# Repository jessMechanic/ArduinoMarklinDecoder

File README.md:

# espMarklinController

## goal

A cheap opensource decoder for the marklin model trains. based on atmelmega micro controller.

## status 

this is currently in a working condintion but open to implovements
this due to my own circumstances has only be tested on a 60651 Marklin Digital Mobil Station Controller.

## current state
- custom addres
- support for lights, sound and general functions keys.

## future plans
a smaller design of the pcb to give support for a wider support
change pcb design to support other than 5v motors (this can currently be fixed by using a jumper wire from the v-in to a lifted leg of the motor driver)

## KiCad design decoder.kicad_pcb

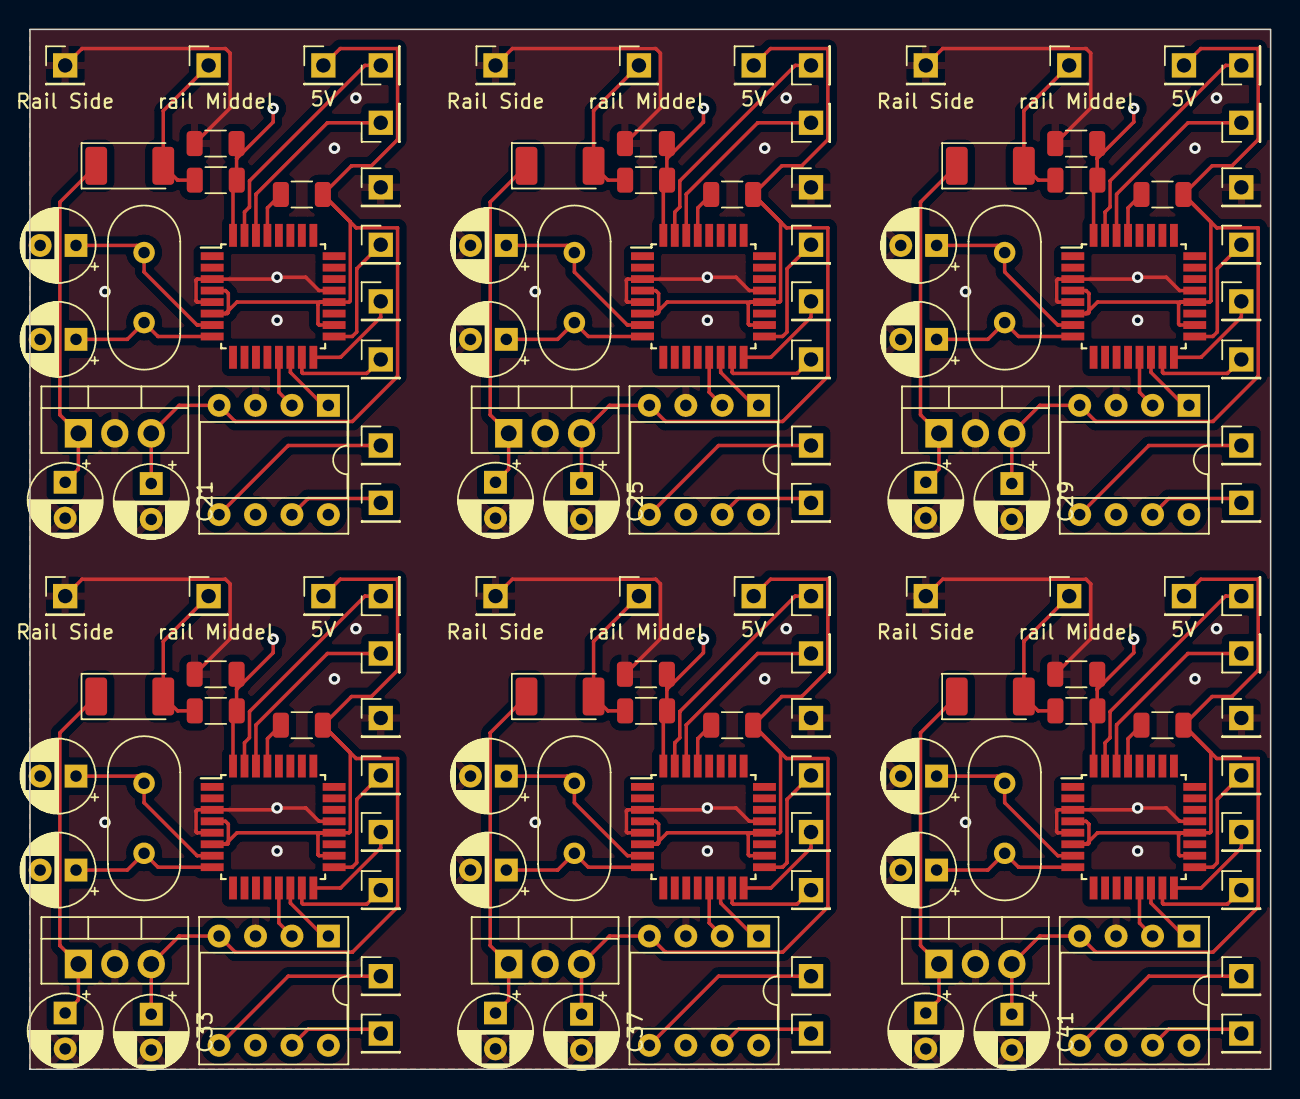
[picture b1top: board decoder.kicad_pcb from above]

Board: 2 copper layers, 86.5 x 72.5 mm, 138 parts (0 on the bottom side), 17 nets.

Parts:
C21, C25, C29, C33, C37, C41: 47uF; CP_Radial_D5.0mm_P2.50mm
C22, C26, C30, C34, C38, C42: 10uF; CP_Radial_D5.0mm_P2.50mm
C23, C24, C27, C28, C31, C32, C35, C36, C39, C40, C43, C44: 22pF; CP_Radial_D5.0mm_P2.50mm
D6, D7, D8, D9, D10, D11: D; D_2010_5025Metric_Pad1.52x2.65mm_HandSolder
R16, R19, R22, R25, R28, R31: 2.2k ohm; R_1206_3216Metric
R17, R18, R20, R21, R23, R24, R26, R27, R29, R30, R32, R33: 1k ohm; R_1206_3216Metric
S56, S67, S78, S89, S100, S111: LED +; PinHeader_1x01_P2.54mm_Vertical
S57, S68, S79, S90, S101, S112: GND; PinHeader_1x01_P2.54mm_Vertical
S58, S69, S80, S91, S102, S113: MotorB; PinHeader_1x01_P2.54mm_Vertical
S59, S70, S81, S92, S103, S114: MotorA; PinHeader_1x01_P2.54mm_Vertical
S60, S71, S82, S93, S104, S115: TX; PinHeader_1x01_P2.54mm_Vertical
S61, S72, S83, S94, S105, S116: RX; PinHeader_1x01_P2.54mm_Vertical
S62, S73, S84, S95, S106, S117: rail Middel; PinHeader_1x01_P2.54mm_Vertical
S63, S74, S85, S96, S107, S118: Rail Side; PinHeader_1x01_P2.54mm_Vertical
S64, S75, S86, S97, S108, S119: MOSI; PinHeader_1x01_P2.54mm_Vertical
S65, S76, S87, S98, S109, S120: MISO; PinHeader_1x01_P2.54mm_Vertical
S66, S77, S88, S99, S110, S121: 5V; PinHeader_1x01_P2.54mm_Vertical
U16, U19, U22, U25, U28, U31: ATmega8-16A; TQFP-32_7x7mm_P0.8mm
U17, U20, U23, U26, U29, U32: LF15_TO220; TO-220-3_Vertical
U18, U21, U24, U27, U30, U33: RZ7886; DIP-8_W7.62mm_Socket
Y6, Y7, Y8, Y9, Y10, Y11: Crystal 16k; Crystal_HC49-4H_Vertical

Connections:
+5V: C21.1, C25.1, C29.1, C33.1, C37.1, C41.1, R18.1, R21.1, R24.1, R27.1, R30.1, R33.1, S66.1 (K), S77.1 (K), S88.1 (K), S99.1 (K), S110.1 (K), S121.1 (K), U16.4 (VCC), U16.6 (VCC), U16.18 (AVCC), U16.20 (AREF), U17.3 (VO), U18.4 (Vcc), U19.4 (VCC), U19.6 (VCC), U19.18 (AVCC), U19.20 (AREF), U20.3 (VO), U21.4 (Vcc), U22.4 (VCC), U22.6 (VCC), U22.18 (AVCC), U22.20 (AREF), U23.3 (VO), U24.4 (Vcc), U25.4 (VCC), U25.6 (VCC), U25.18 (AVCC), U25.20 (AREF), U26.3 (VO), U27.4 (Vcc), U28.4 (VCC), U28.6 (VCC), U28.18 (AVCC), U28.20 (AREF), U29.3 (VO), U30.4 (Vcc), U31.4 (VCC), U31.6 (VCC), U31.18 (AVCC), U31.20 (AREF), U32.3 (VO), U33.4 (Vcc)
BI: U16.14 (PB2), U18.1 (BI), U19.14 (PB2), U21.1 (BI), U22.14 (PB2), U24.1 (BI), U25.14 (PB2), U27.1 (BI), U28.14 (PB2), U30.1 (BI), U31.14 (PB2), U33.1 (BI)
FI: U16.13 (PB1), U18.2 (FI), U19.13 (PB1), U21.2 (FI), U22.13 (PB1), U24.2 (FI), U25.13 (PB1), U27.2 (FI), U28.13 (PB1), U30.2 (FI), U31.13 (PB1), U33.2 (FI)
GND: C21.2, C22.2, C23.2, C24.2, C25.2, C26.2, C27.2, C28.2, C29.2, C30.2, C31.2, C32.2, C33.2, C34.2, C35.2, C36.2, C37.2, C38.2, C39.2, C40.2, C41.2, C42.2, C43.2, C44.2, R17.2, R20.2, R23.2, R26.2, R29.2, R32.2, S57.1 (K), S63.1 (K), S68.1 (K), S74.1 (K), S79.1 (K), S85.1 (K), S90.1 (K), S96.1 (K), S101.1 (K), S107.1 (K), S112.1 (K), S118.1 (K), U16.3 (GND), U16.5 (GND), U16.21 (AGND), U17.2 (GND), U18.3 (GND), U19.3 (GND), U19.5 (GND), U19.21 (AGND), U20.2 (GND), U21.3 (GND), U22.3 (GND), U22.5 (GND), U22.21 (AGND), U23.2 (GND), U24.3 (GND), U25.3 (GND), U25.5 (GND), U25.21 (AGND), U26.2 (GND), U27.3 (GND), U28.3 (GND), U28.5 (GND), U28.21 (AGND), U29.2 (GND), U30.3 (GND), U31.3 (GND), U31.5 (GND), U31.21 (AGND), U32.2 (GND), U33.3 (GND)
unnamed: C22.1, C26.1, C30.1, C34.1, C38.1, C42.1, D6.1 (K), D7.1 (K), D8.1 (K), D9.1 (K), D10.1 (K), D11.1 (K), U17.1 (VI), U20.1 (VI), U23.1 (VI), U26.1 (VI), U29.1 (VI), U32.1 (VI)
unnamed: S56.1 (K), S67.1 (K), S78.1 (K), S89.1 (K), S100.1 (K), S111.1 (K), U16.17 (PB5), U19.17 (PB5), U22.17 (PB5), U25.17 (PB5), U28.17 (PB5), U31.17 (PB5)
unnamed: S58.1 (K), S69.1 (K), S80.1 (K), S91.1 (K), S102.1 (K), S113.1 (K), U18.7 (BO), U21.7 (BO), U24.7 (BO), U27.7 (BO), U30.7 (BO), U33.7 (BO)
unnamed: S59.1 (K), S70.1 (K), S81.1 (K), S92.1 (K), S103.1 (K), S114.1 (K), U18.5 (FO), U21.5 (FO), U24.5 (FO), U27.5 (FO), U30.5 (FO), U33.5 (FO)
unnamed: S60.1 (K), S71.1 (K), S82.1 (K), S93.1 (K), S104.1 (K), S115.1 (K), U16.31 (PD1), U19.31 (PD1), U22.31 (PD1), U25.31 (PD1), U28.31 (PD1), U31.31 (PD1)
unnamed: S61.1 (K), S72.1 (K), S83.1 (K), S94.1 (K), S105.1 (K), S116.1 (K), U16.30 (PD0), U19.30 (PD0), U22.30 (PD0), U25.30 (PD0), U28.30 (PD0), U31.30 (PD0)
unnamed: S64.1 (K), S75.1 (K), S86.1 (K), S97.1 (K), S108.1 (K), S119.1 (K), U16.15 (PB3), U19.15 (PB3), U22.15 (PB3), U25.15 (PB3), U28.15 (PB3), U31.15 (PB3)
unnamed: S65.1 (K), S76.1 (K), S87.1 (K), S98.1 (K), S109.1 (K), S120.1 (K), U16.16 (PB4), U19.16 (PB4), U22.16 (PB4), U25.16 (PB4), U28.16 (PB4), U31.16 (PB4)
unnamed: C23.1, C27.1, C31.1, C35.1, C39.1, C43.1, U16.7 (PB6/XTAL1), U19.7 (PB6/XTAL1), U22.7 (PB6/XTAL1), U25.7 (PB6/XTAL1), U28.7 (PB6/XTAL1), U31.7 (PB6/XTAL1), Y6.1, Y7.1, Y8.1, Y9.1, Y10.1, Y11.1
unnamed: C24.1, C28.1, C32.1, C36.1, C40.1, C44.1, U16.8 (PB7/XTAL2), U19.8 (PB7/XTAL2), U22.8 (PB7/XTAL2), U25.8 (PB7/XTAL2), U28.8 (PB7/XTAL2), U31.8 (PB7/XTAL2), Y6.2, Y7.2, Y8.2, Y9.2, Y10.2, Y11.2
unnamed: R18.2, R21.2, R24.2, R27.2, R30.2, R33.2, U16.29 (PC6/~RESET), U19.29 (PC6/~RESET), U22.29 (PC6/~RESET), U25.29 (PC6/~RESET), U28.29 (PC6/~RESET), U31.29 (PC6/~RESET)
Signal: R16.2, R17.1, R19.2, R20.1, R22.2, R23.1, R25.2, R26.1, R28.2, R29.1, R31.2, R32.1, U16.32 (PD2), U19.32 (PD2), U22.32 (PD2), U25.32 (PD2), U28.32 (PD2), U31.32 (PD2)
VCC: D6.2 (A), D7.2 (A), D8.2 (A), D9.2 (A), D10.2 (A), D11.2 (A), R16.1, R19.1, R22.1, R25.1, R28.1, R31.1, S62.1 (K), S73.1 (K), S84.1 (K), S95.1 (K), S106.1 (K), S117.1 (K)

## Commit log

2024-01-24 Added incoding functions
2024-01-25 Updated encoding functions
2024-10-10 Implimented marklin delta / motorola signal
2024-10-10 Added intergration with mp3 player ic for horn and sound effects
2024-10-10 Added pcb designes
2024-10-10 Added fix for 5v+ motors
